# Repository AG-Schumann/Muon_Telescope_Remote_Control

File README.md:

# Muon Telescope Remote Control

A four-panel plastic-scintillator cosmic-ray muon telescope that rotates in zenith angle under software control, built around a Raspberry Pi 4.

**Documentation:** https://AG-Schumann.github.io/Muon_Telescope_Remote_Control/ — hardware, installation, architecture, configuration reference, data formats, calibration, troubleshooting.

```
software/   the Python package (daemon, TUI, drivers), config, scripts, systemd unit
hardware/   KiCad board designs, CAD, measurement-setup drawings and photos
docs/       the documentation site (GitHub Pages, Jekyll + just-the-docs)
```

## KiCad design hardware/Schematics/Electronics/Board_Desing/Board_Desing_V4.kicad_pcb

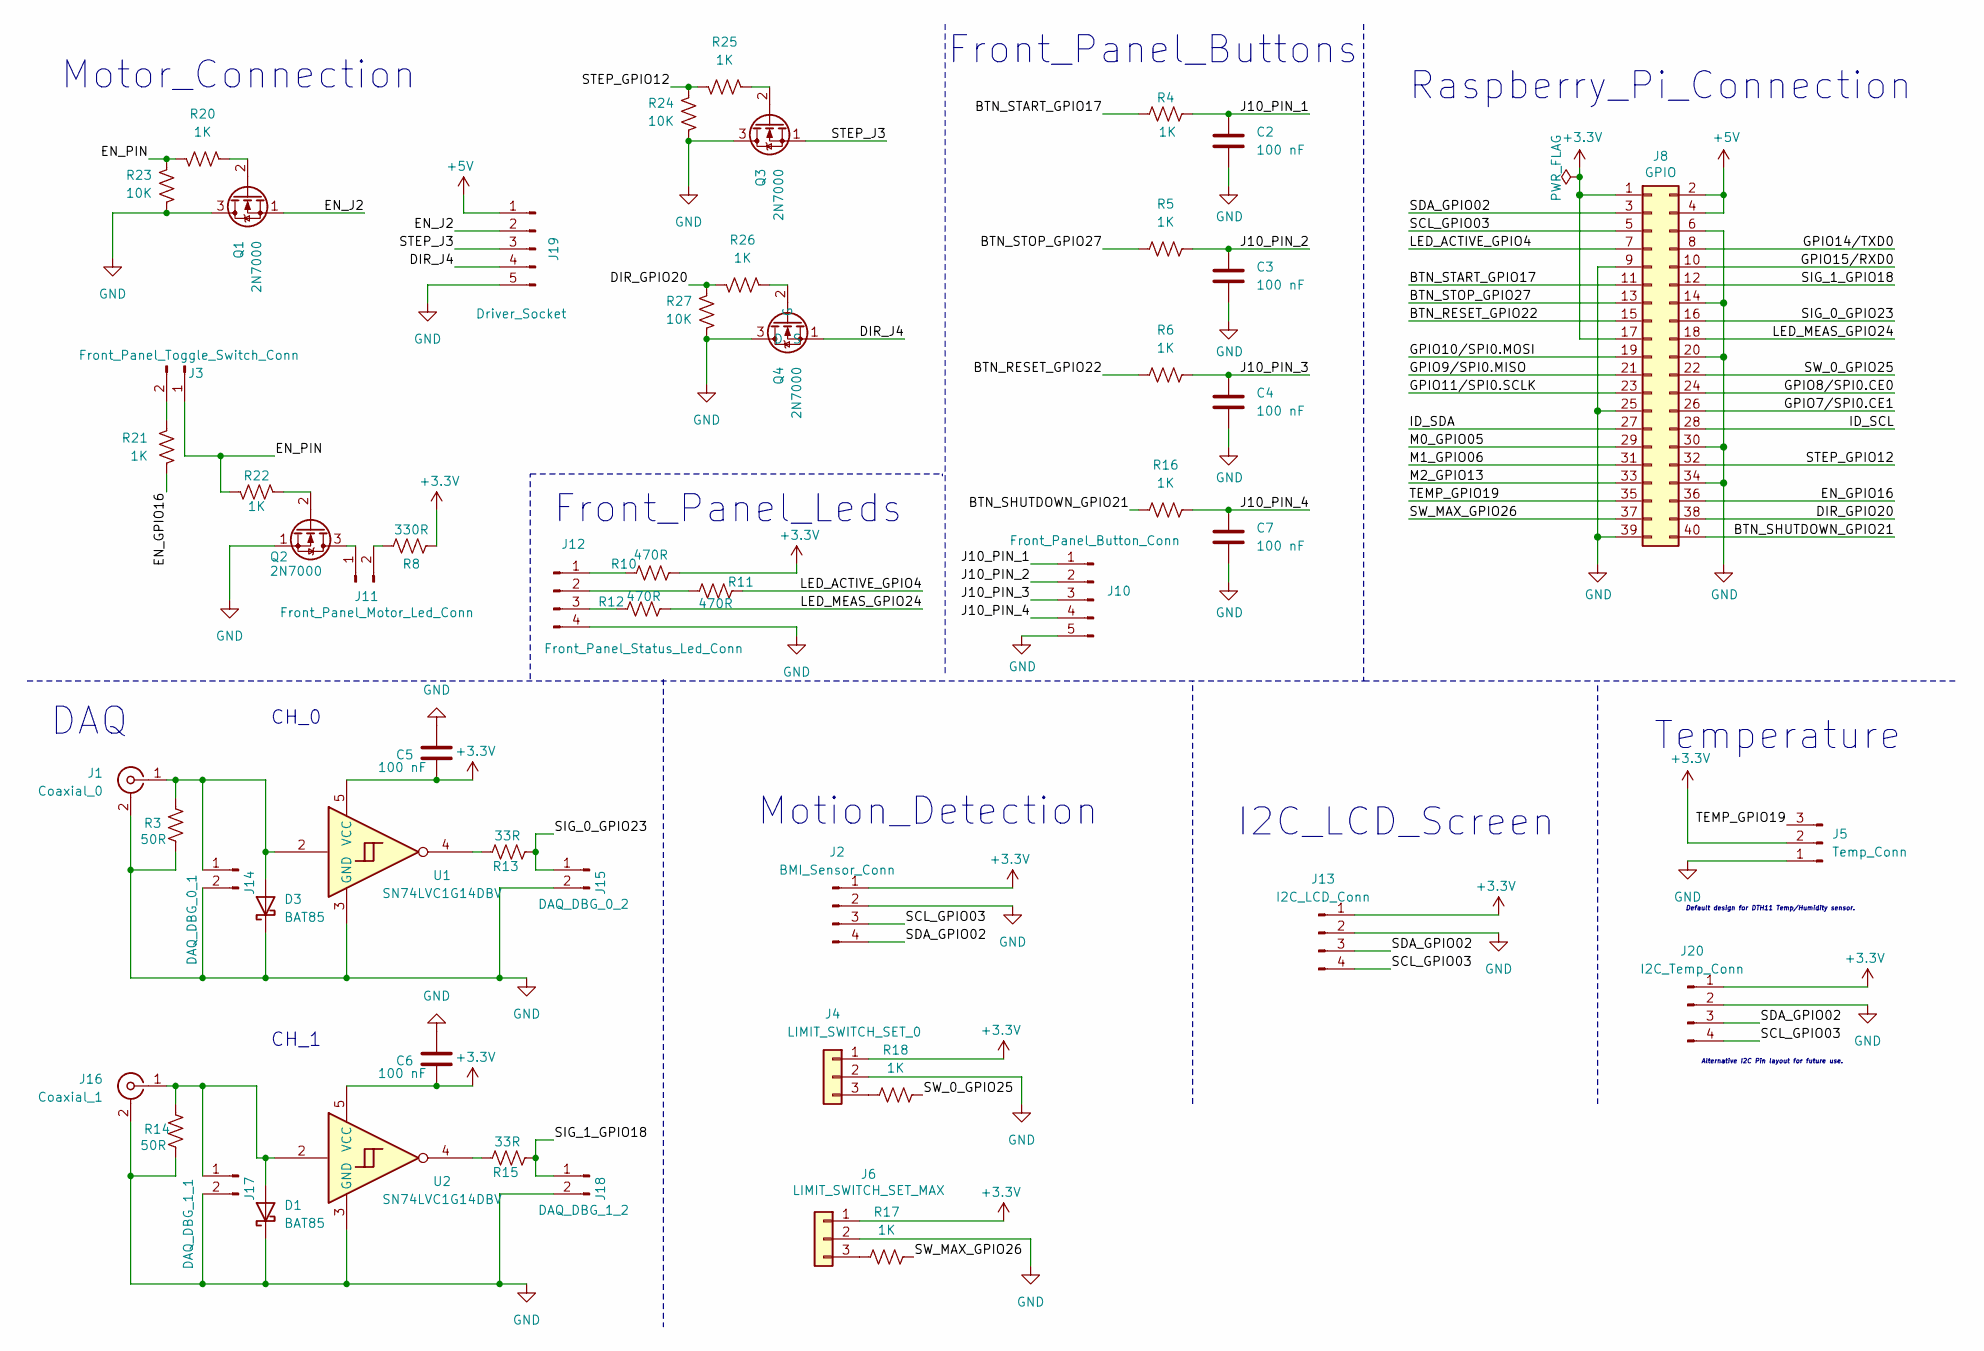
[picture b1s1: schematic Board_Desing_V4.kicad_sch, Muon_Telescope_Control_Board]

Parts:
C2, C3, C4, C5, C6, C7: 100 nF; C_Disc_D5.0mm_W2.5mm_P5.00mm
D1, D3: BAT85; D_DO-34_SOD68_P7.62mm_Horizontal
J1: Coaxial_0; LEMO-EPL.00.250.NTN
J2: BMI_Sensor_Conn; PinSocket_1x04_P2.54mm_Vertical
J3: Front_Panel_Toggle_Switch_Conn; PinHeader_1x02_P2.54mm_Vertical
J4: LIMIT_SWITCH_SET_0; PinHeader_1x03_P2.54mm_Vertical
J5: Temp_Conn; PinHeader_1x03_P2.54mm_Vertical
J6: LIMIT_SWITCH_SET_MAX; PinHeader_1x03_P2.54mm_Vertical
J8: GPIO; PinSocket_2x20_P2.54mm_Vertical
J10: Front_Panel_Button_Conn; PinSocket_1x05_P2.54mm_Vertical
J11: Front_Panel_Motor_Led_Conn; PinHeader_1x02_P2.54mm_Vertical
J12: Front_Panel_Status_Led_Conn; PinSocket_1x04_P2.54mm_Vertical
J13: I2C_LCD_Conn; PinSocket_1x04_P2.54mm_Vertical
J14: DAQ_DBG_0_1; PinHeader_1x02_P2.54mm_Vertical
J15: DAQ_DBG_0_2; PinHeader_1x02_P2.54mm_Vertical
J16: Coaxial_1; LEMO-EPL.00.250.NTN
J17: DAQ_DBG_1_1; PinHeader_1x02_P2.54mm_Vertical
J18: DAQ_DBG_1_2; PinHeader_1x02_P2.54mm_Vertical
J19: Driver_Socket; PinHeader_1x05_P2.54mm_Vertical
J20: I2C_Temp_Conn; PinSocket_1x04_P2.54mm_Vertical
Q1, Q2, Q3, Q4: 2N7000; TO-92
R3, R14: 50R; R_Axial_DIN0207_L6.3mm_D2.5mm_P10.16mm_Horizontal
R4, R5, R6, R16, R17, R18, R20, R21, R22, R25, R26: 1K; R_Axial_DIN0207_L6.3mm_D2.5mm_P10.16mm_Horizontal
R8: 330R; R_Axial_DIN0207_L6.3mm_D2.5mm_P10.16mm_Horizontal
R10, R11, R12: 470R; R_Axial_DIN0207_L6.3mm_D2.5mm_P10.16mm_Horizontal
R13, R15: 33R; R_Axial_DIN0207_L6.3mm_D2.5mm_P10.16mm_Horizontal
R23, R24, R27: 10K; R_Axial_DIN0207_L6.3mm_D2.5mm_P10.16mm_Horizontal
U1, U2: SN74LVC1G14DBV; SOT-23-5_HandSoldering

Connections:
+3.3V: C5.1, C6.1, J2.1, J4.1, J5.2, J6.1, J8.1, J8.17, J13.1, J20.1, R8.1, R10.2, U1.5 (VCC), U2.5 (VCC)
+5V: J8.2, J8.4, J19.1; also elsewhere on the board
/BTN_RESET_GPIO22: J8.15, R6.1
/BTN_SHUTDOWN_GPIO21: J8.40, R16.1
/BTN_START_GPIO17: J8.11, R4.1
/BTN_STOP_GPIO27: J8.13, R5.1
/DIR_GPIO20: J8.38, R26.2, R27.1
/DIR_J4: J19.4, Q4.1 (S)
/EN_GPIO16: J8.36, R21.1
/EN_J2: J19.2, Q1.1 (S)
/EN_PIN: J3.1, R20.2, R22.2, R23.1
/GPIO7/SPI0.CE1: J8.26
/GPIO8/SPI0.CE0: J8.24
/GPIO9/SPI0.MISO: J8.21
/GPIO10/SPI0.MOSI: J8.19
/GPIO11/SPI0.SCLK: J8.23
/GPIO14/TXD0: J8.8
/GPIO15/RXD0: J8.10
/ID_SCL: J8.28
/ID_SDA: J8.27
/J10_PIN_1: C2.1, J10.1, R4.2
/J10_PIN_2: C3.1, J10.2, R5.2
/J10_PIN_3: C4.1, J10.3, R6.2
/J10_PIN_4: C7.1, J10.4, R16.2
/LED_ACTIVE_GPIO4: J8.7, R11.2
/LED_MEAS_GPIO24: J8.18, R12.2
/M0_GPIO05: J8.29
/M1_GPIO06: J8.31
/M2_GPIO13: J8.33
/SCL_GPIO03: J2.3, J8.5, J13.4, J20.4
/SDA_GPIO02: J2.4, J8.3, J13.3, J20.3
/SIG_0_GPIO23: J8.16, J15.1, R13.1
/SIG_1_GPIO18: J8.12, J18.1, R15.1
/STEP_GPIO12: J8.32, R24.1, R25.2
/STEP_J3: J19.3, Q3.1 (S)
/SW_0_GPIO25: J8.22, R18.2
/SW_MAX_GPIO26: J8.37, R17.2
/TEMP_GPIO19: J5.3, J8.35
GND: C2.2, C3.2, C4.2, C5.2, C6.2, C7.2, D1.1 (K), D3.1 (K), J1.2 (Ext), J2.2, J4.2, J5.1, J6.2, J8.6, J8.9, J8.14, J8.20, J8.25, J8.30, J8.34, J8.39, J10.5, J12.4, J13.2, J14.2, J15.2, J16.2 (Ext), J17.2, J18.2, J19.5, J20.2, Q1.3 (D), Q2.1 (S), Q3.3 (D), Q4.3 (D), R3.1, R14.1, R23.2, R24.2, R27.2, U1.3 (GND), U2.3 (GND); also elsewhere on the board
unnamed: D1.2 (A), J16.1 (In), J17.1, R14.2, U2.2
unnamed: D3.2 (A), J1.1 (In), J14.1, R3.2, U1.2
unnamed: J3.2, R21.2
unnamed: J4.3, R18.1
unnamed: J6.3, R17.1
unnamed: J11.1, Q2.3 (D)
unnamed: J11.2, R8.2
unnamed: J12.1, R10.1
unnamed: J12.2, R11.1
unnamed: J12.3, R12.1
unnamed: Q1.2 (G), R20.1
unnamed: Q2.2 (G), R22.1
unnamed: Q3.2 (G), R25.1
unnamed: Q4.2 (G), R26.1
unnamed: R13.2, U1.4
unnamed: R15.2, U2.4

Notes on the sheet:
CH_0
Front_Panel_Leds
Raspberry_Pi_Connection
Temperature
Front_Panel_Buttons
Motion_Detection
I2C_LCD_Screen
DAQ
Alternative I2C Pin layout for future use.
Motor_Connection
CH_1
Default design for DTH11 Temp/Humidity sensor.

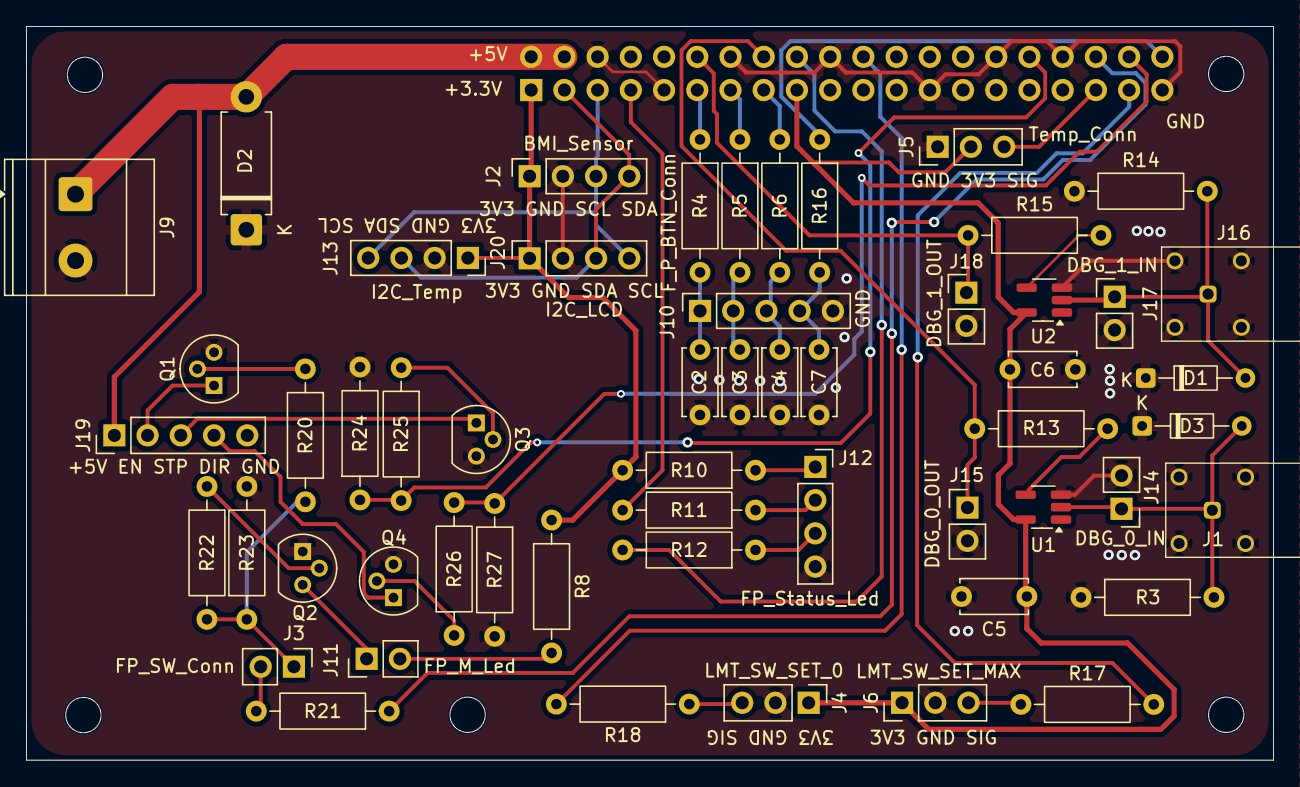
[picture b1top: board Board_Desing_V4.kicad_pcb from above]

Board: 2 copper layers, 95.3 x 56.1 mm, 61 parts (1 on the bottom side), 43 nets.

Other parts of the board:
D2: P6KE6.8A; D_DO-15_P10.16mm_Horizontal
J9: Screw_Terminal_01x02; TerminalBlock_Phoenix_MKDS-3-2-5.08_1x02_P5.08mm_Horizontal
MH2, MH3, MH3#2, MH3#3, MH4: MountingHole_2.7mm_M2.5

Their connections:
+5V: D2.2 (A2), J9.1; also elsewhere on the board
GND: D2.1 (A1), J9.2; also elsewhere on the board
